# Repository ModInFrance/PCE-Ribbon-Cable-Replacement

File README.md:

# PCE-Ribbon-Cable-Replacement V2
A clean and simple solution to replace the massive ribbon cable in the PCE and Core Grafx.

This project is open source (please read the license). You can make your own or <a href="https://shop.modinfrance.fr/en/home/56-pc-engine-ribbon-cable-replacement.html" target="_blank">buy it from my store</a>.

The Original PCE (white) and the 2 CoreGrafx (blue and orange) remain beautiful pieces pf hardware after all those years.
However they have one major imperfection: The card connector and the main PCB are connected by a huge ribbon cable. This Ribbon cable tends to oxidize and break like a sheet of paper when opening the console.

This is why I created a replacement using two small PCBs and a single 45 pins FFC cable. The result is not only esthetically pleasing but also future proof.

<b>[UPDATE 12/01/2023]</b>
<b><u>V2 is out with a much smaller, leaner design</u></b>

<b><u>New pins - 2.5 mm</u></b>
I had some new pin array produced especially for the project. 2.5 pitch, 21 pins, extremely short upper pin. It removes most of the issues below, including the need for an isolation foam and trimming the pins. This is dead cheap, so contact me if you need some!

<b>CHALLENGES AND LIMITS OF THE SOLUTION</b>

- 2.5mm pitch<br />
Even though this is a relatively simple design the main challenge rest on the fact that the original Ribbon cable uses non-standard 2.5mm pitch when most of the hardware you can find out there is 2.54mm.
There is no magic solution but it's relatively easy to overcome the issue using standard 2.54 pin array and cutting them in half.

- PCBs contact<br />
Second issue is that the new cartridge connector PCB is sitting right on top the PCE extention connector when shell is closed. There can be contacts. This can easily be fixed with a 0.6mm PCB, a good trim of the pin arrays and, to be absolutely safe, adding a layer of foam on the extension port.

<b>INSTALLATION GUIDE</b>

Step 1 is to remove the original ribbon cable and believe me this is the hardest part of the mod. Take your time and don't pull too hard, you don't want too pull a pad or a trace.

Now get the kit. It should look like this (with an added piece of sticky foam). 

I suggest testing continuity now to make sure there was no error when soldering the Molex connector:
- Each PCB have 2 lines P101 and P102 and each line has 21 pins. 
- With the ribbon cable in. Pin 101-1 on the mobo adapter PCB should have good contact with Pin 101-1 on the catridge adapter PCB and the same for the other 41 pins

Now cut 2 11 pins long array and 2 10 pins array like this:

Trim the side of your arrays so that they can fit the PCE cartridge PCB (DO NOT SOLDER IT AT THIS STAGE)

You should have 2 very close pins due to the cut and the difference of pitch. 

Use your favorite clamp to bend them slightly so that you can nicely fit in the adapter PCB.

Solder all 42 pins on the top side of the adapter PCB

Trim the top of the soldered pins as short as possible

Repeat the process with the second adapter PCB and the Mobo of the PCE (and again remember to trim the soldered pins)

- And Finally solder the bottom side of the PCB
- Add the provided piece of foam to avoid contact with the extension port
- Connect the flat cable
- It should now look like this:

Last step : Play Jackie Chan's Action Kung Fu for the next 20 years.

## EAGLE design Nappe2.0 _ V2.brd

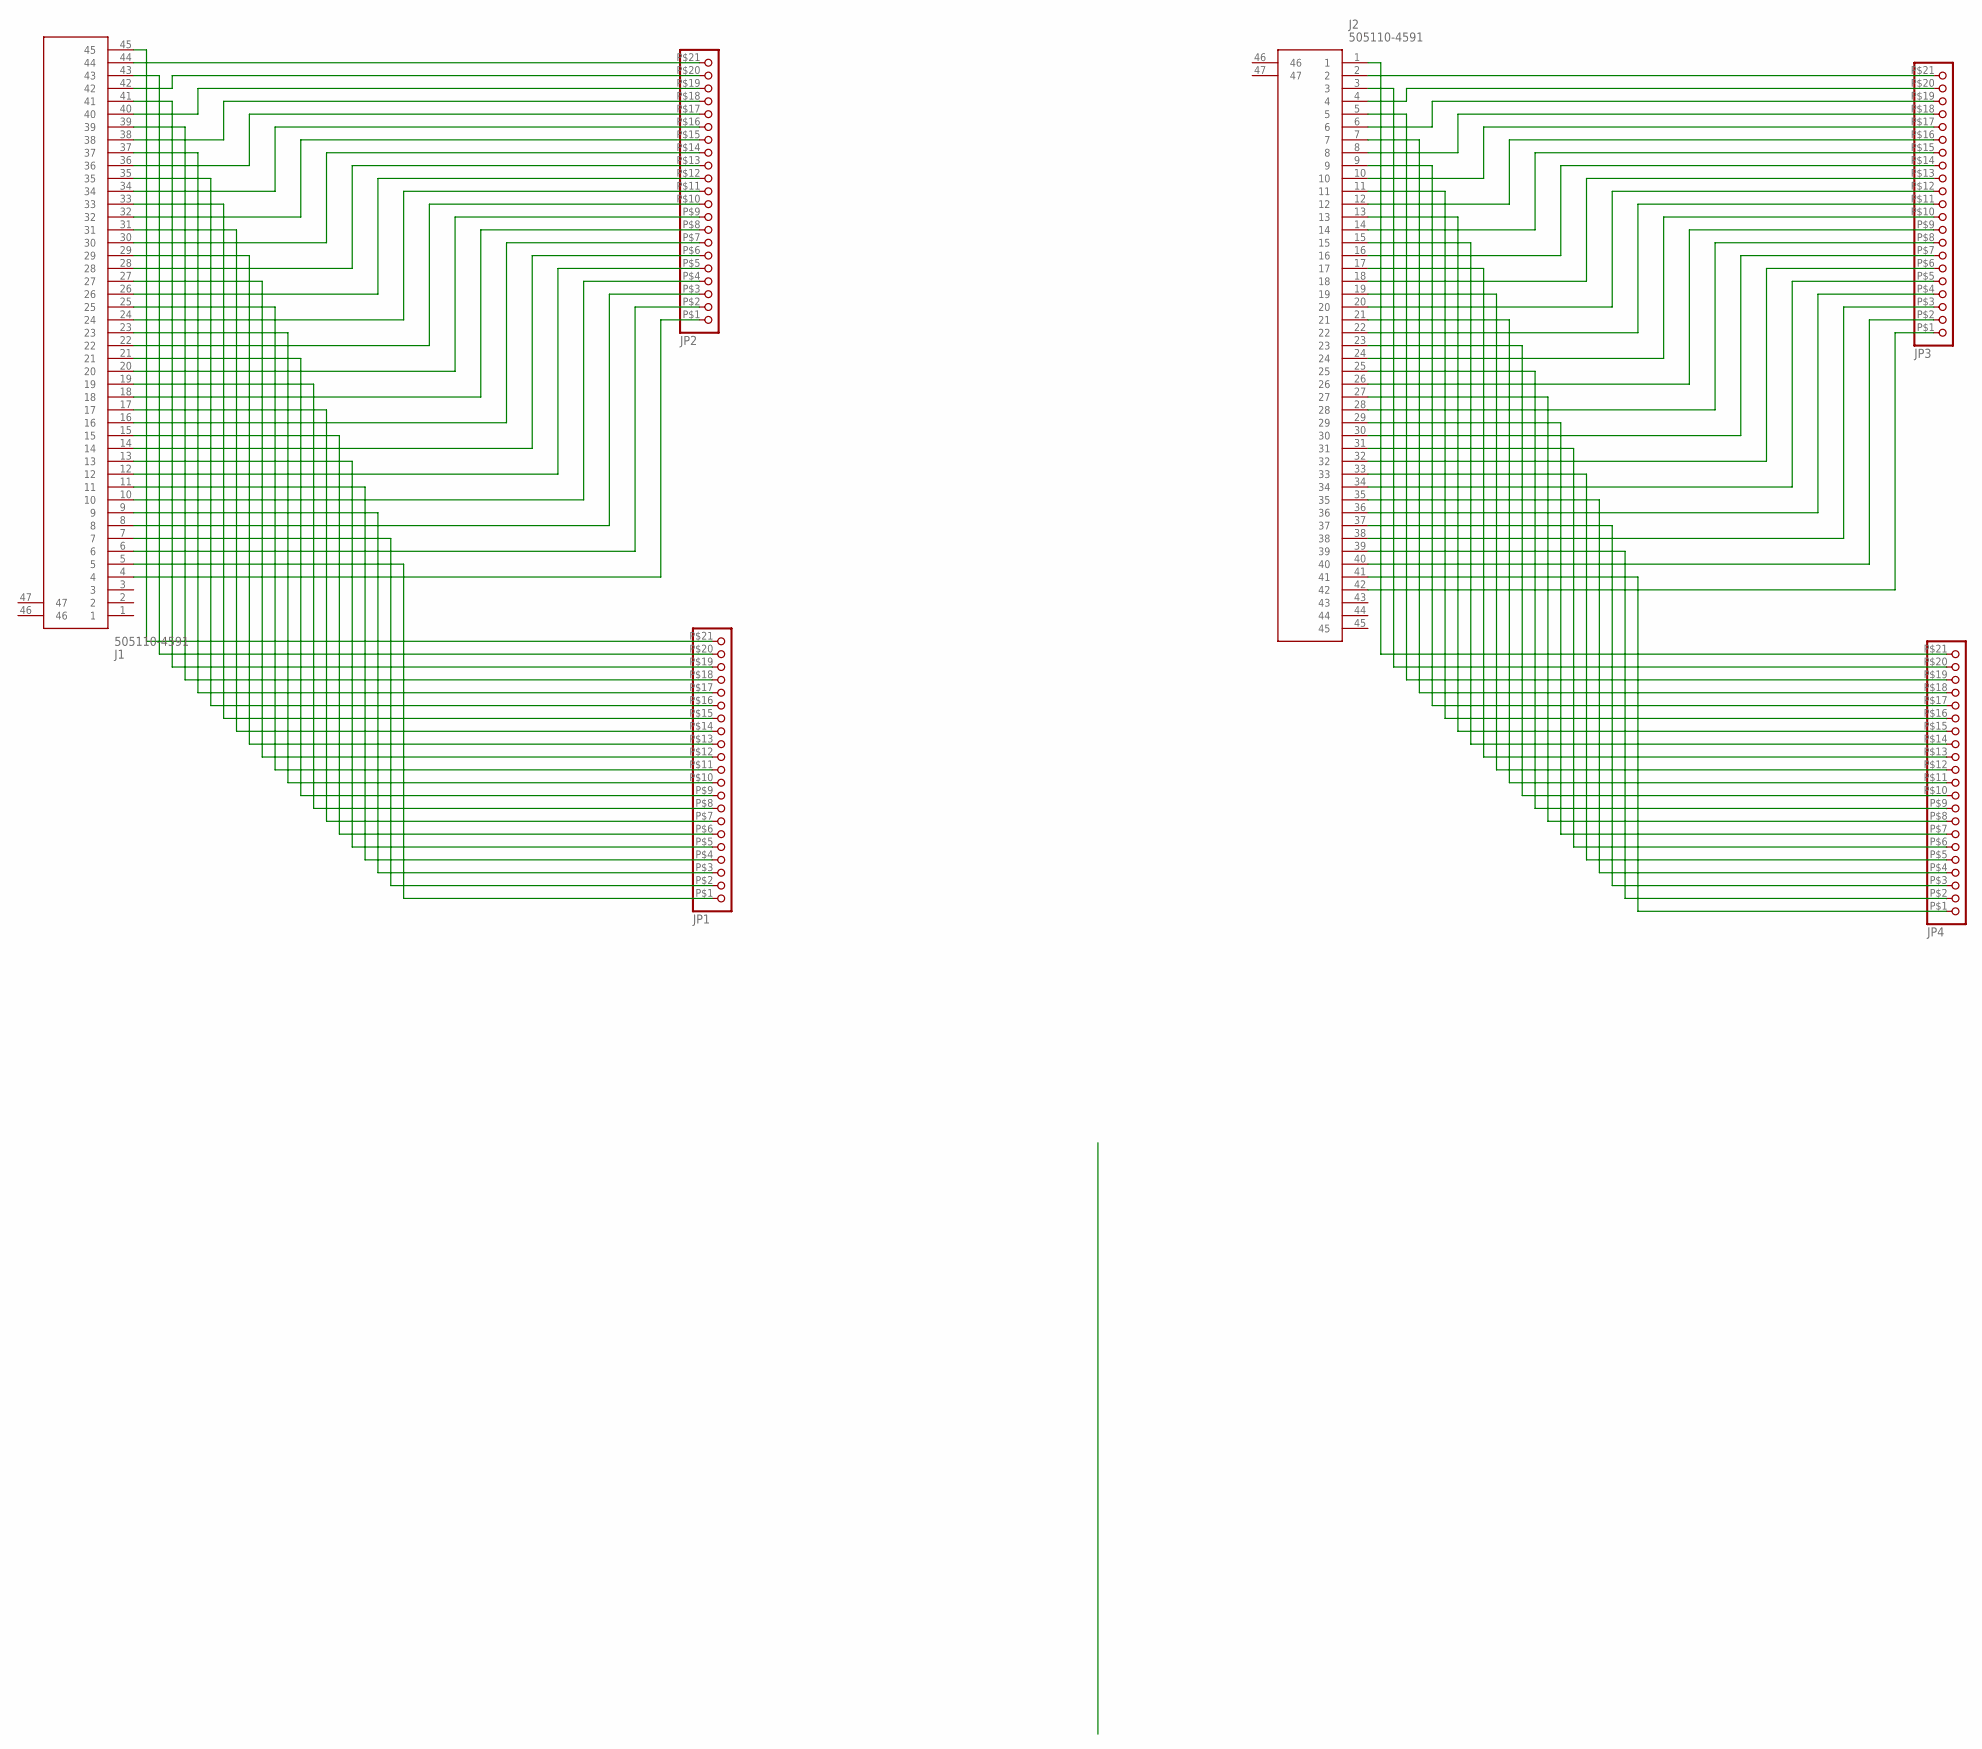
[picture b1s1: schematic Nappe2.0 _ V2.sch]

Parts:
J1, J2: 505110-4591; 5051104591
JP1, JP2, JP3, JP4: PINHD-1X21(2.5); 1X21(2.5)

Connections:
unnamed: J2.2, JP3.P$21 (21)
unnamed: J2.3, JP4.P$20 (20)
unnamed: J2.26, JP3.P$9 (9)
unnamed: J2.4, JP3.P$20 (20)
unnamed: J2.6, JP3.P$19 (19)
unnamed: J2.28, JP3.P$8 (8)
unnamed: J2.18, JP3.P$13 (13)
unnamed: J2.8, JP3.P$18 (18)
unnamed: J2.10, JP3.P$17 (17)
unnamed: J2.12, JP3.P$16 (16)
unnamed: J2.14, JP3.P$15 (15)
unnamed: J2.16, JP3.P$14 (14)
unnamed: J2.20, JP3.P$12 (12)
unnamed: J2.22, JP3.P$11 (11)
unnamed: J2.24, JP3.P$10 (10)
unnamed: J2.30, JP3.P$7 (7)
unnamed: J2.32, JP3.P$6 (6)
unnamed: J2.34, JP3.P$5 (5)
unnamed: J2.36, JP3.P$4 (4)
unnamed: J2.42, JP3.P$1 (1)
unnamed: J2.40, JP3.P$2 (2)
unnamed: J2.38, JP3.P$3 (3)
unnamed: J2.1, JP4.P$21 (21)
unnamed: J2.5, JP4.P$19 (19)
unnamed: J2.7, JP4.P$18 (18)
unnamed: J2.9, JP4.P$17 (17)
unnamed: J2.11, JP4.P$16 (16)
unnamed: J2.13, JP4.P$15 (15)
unnamed: J2.15, JP4.P$14 (14)
unnamed: J2.17, JP4.P$13 (13)
unnamed: J2.41, JP4.P$1 (1)
unnamed: J1.44, JP2.P$21 (21)
unnamed: J1.42, JP2.P$20 (20)
unnamed: J1.40, JP2.P$19 (19)
unnamed: J2.27, JP4.P$8 (8)
unnamed: J1.38, JP2.P$18 (18)
unnamed: J1.36, JP2.P$17 (17)
unnamed: J2.33, JP4.P$5 (5)
unnamed: J1.34, JP2.P$16 (16)
unnamed: J1.32, JP2.P$15 (15)
unnamed: J2.21, JP4.P$11 (11)
unnamed: J2.23, JP4.P$10 (10)
unnamed: J2.25, JP4.P$9 (9)
unnamed: J1.30, JP2.P$14 (14)
unnamed: J2.29, JP4.P$7 (7)
unnamed: J2.31, JP4.P$6 (6)
unnamed: J2.39, JP4.P$2 (2)
unnamed: J2.37, JP4.P$3 (3)
unnamed: J2.35, JP4.P$4 (4)
unnamed: J2.19, JP4.P$12 (12)
unnamed: J1.28, JP2.P$13 (13)
unnamed: J1.26, JP2.P$12 (12)
unnamed: J1.24, JP2.P$11 (11)
unnamed: J1.22, JP2.P$10 (10)
unnamed: J1.20, JP2.P$9 (9)
unnamed: J1.18, JP2.P$8 (8)
unnamed: J1.16, JP2.P$7 (7)
unnamed: J1.14, JP2.P$6 (6)
unnamed: J1.12, JP2.P$5 (5)
unnamed: J1.10, JP2.P$4 (4)
unnamed: J1.6, JP2.P$2 (2)
unnamed: J1.8, JP2.P$3 (3)
unnamed: J1.4, JP2.P$1 (1)
unnamed: J1.45, JP1.P$21 (21)
unnamed: J1.43, JP1.P$20 (20)
unnamed: J1.41, JP1.P$19 (19)
unnamed: J1.39, JP1.P$18 (18)
unnamed: J1.37, JP1.P$17 (17)
unnamed: J1.35, JP1.P$16 (16)
unnamed: J1.33, JP1.P$15 (15)
unnamed: J1.31, JP1.P$14 (14)
unnamed: J1.29, JP1.P$13 (13)
unnamed: J1.19, JP1.P$8 (8)
unnamed: J1.25, JP1.P$11 (11)
unnamed: J1.23, JP1.P$10 (10)
unnamed: J1.21, JP1.P$9 (9)
unnamed: J1.17, JP1.P$7 (7)
unnamed: J1.15, JP1.P$6 (6)
unnamed: J1.13, JP1.P$5 (5)
unnamed: J1.7, JP1.P$2 (2)
unnamed: J1.9, JP1.P$3 (3)
unnamed: J1.11, JP1.P$4 (4)
unnamed: J1.27, JP1.P$12 (12)
unnamed: J1.5, JP1.P$1 (1)

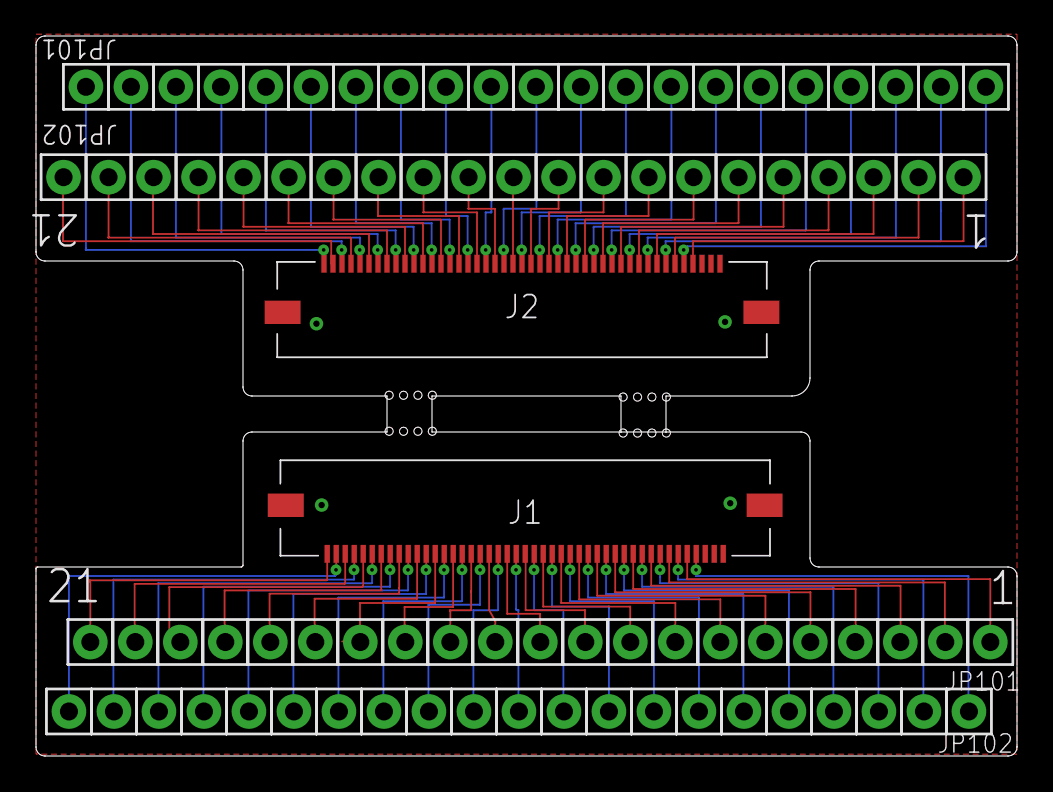
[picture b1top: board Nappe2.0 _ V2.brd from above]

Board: 2 copper layers, 54.5 x 40.0 mm, 6 parts (0 on the bottom side), 84 nets.

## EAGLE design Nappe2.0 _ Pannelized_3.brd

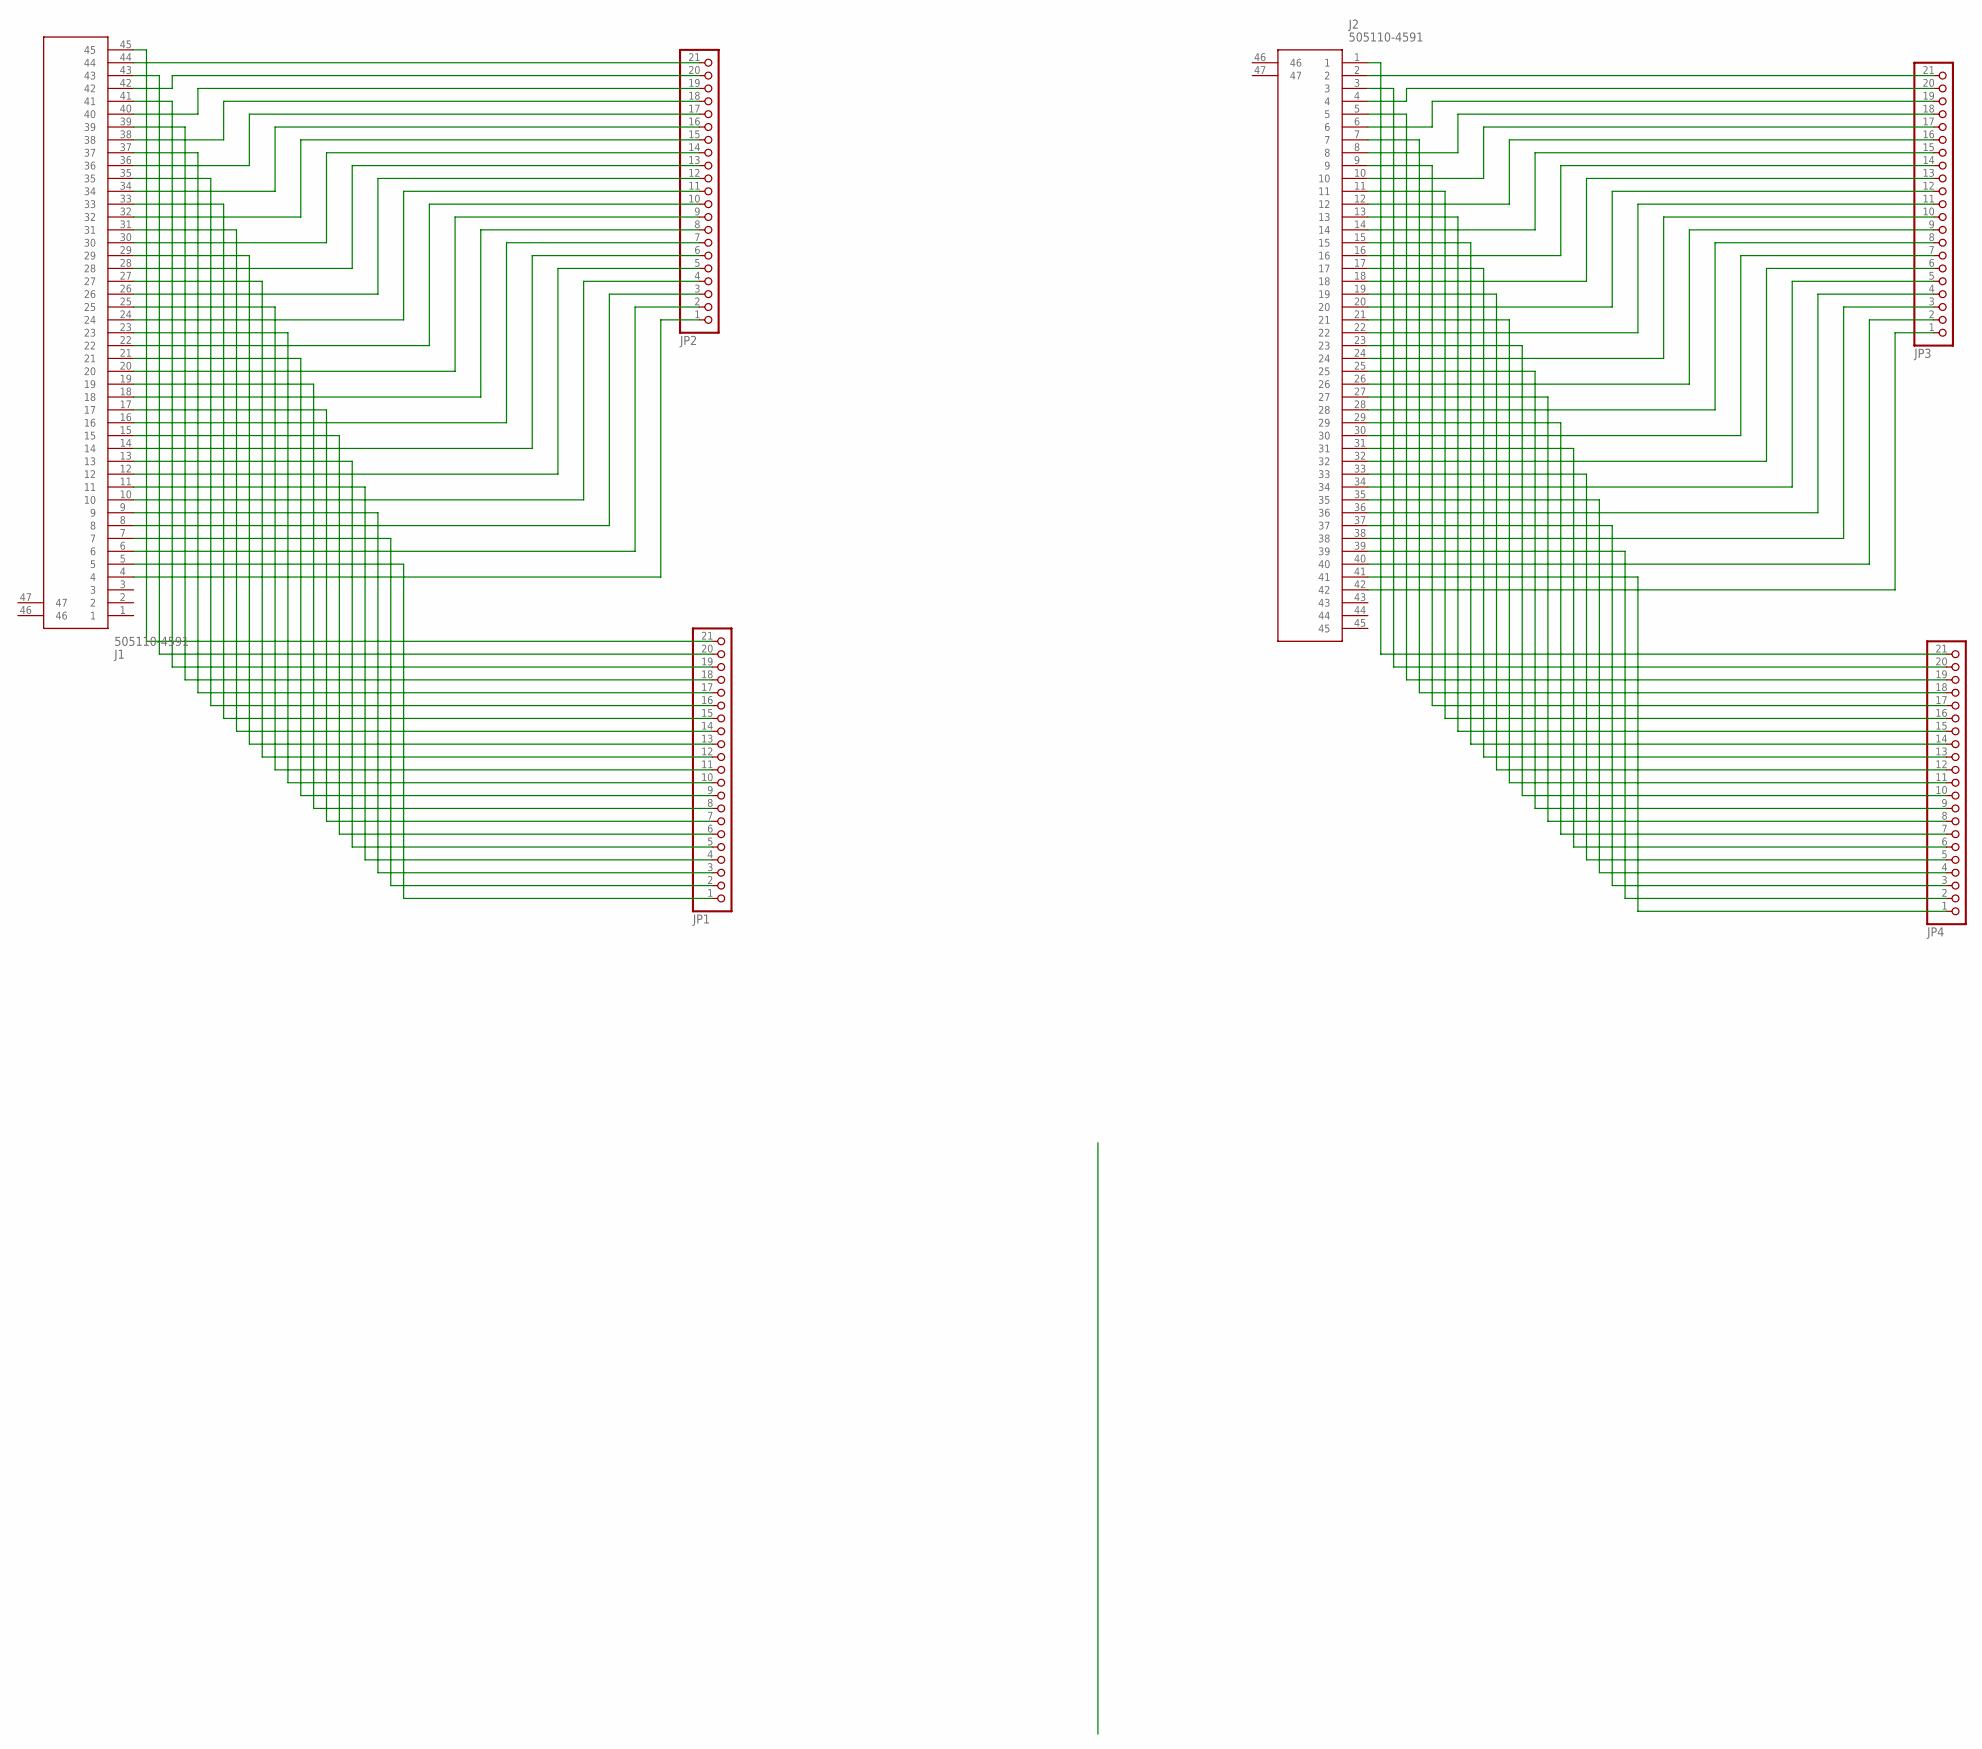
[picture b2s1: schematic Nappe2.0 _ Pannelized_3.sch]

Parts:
J1, J2: 505110-4591; 5051104591
JP1, JP2, JP3, JP4: PINHD-1X21(2.4); 1X21(2.4)

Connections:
unnamed: J2.2, JP3.21
unnamed: J2.3, JP4.20
unnamed: J2.26, JP3.9
unnamed: J2.4, JP3.20
unnamed: J2.6, JP3.19
unnamed: J2.28, JP3.8
unnamed: J2.18, JP3.13
unnamed: J2.8, JP3.18
unnamed: J2.10, JP3.17
unnamed: J2.12, JP3.16
unnamed: J2.14, JP3.15
unnamed: J2.16, JP3.14
unnamed: J2.20, JP3.12
unnamed: J2.22, JP3.11
unnamed: J2.24, JP3.10
unnamed: J2.30, JP3.7
unnamed: J2.32, JP3.6
unnamed: J2.34, JP3.5
unnamed: J2.36, JP3.4
unnamed: J2.42, JP3.1
unnamed: J2.40, JP3.2
unnamed: J2.38, JP3.3
unnamed: J2.1, JP4.21
unnamed: J2.5, JP4.19
unnamed: J2.7, JP4.18
unnamed: J2.9, JP4.17
unnamed: J2.11, JP4.16
unnamed: J2.13, JP4.15
unnamed: J2.15, JP4.14
unnamed: J2.17, JP4.13
unnamed: J2.41, JP4.1
unnamed: J1.44, JP2.21
unnamed: J1.42, JP2.20
unnamed: J1.40, JP2.19
unnamed: J2.27, JP4.8
unnamed: J1.38, JP2.18
unnamed: J1.36, JP2.17
unnamed: J2.33, JP4.5
unnamed: J1.34, JP2.16
unnamed: J1.32, JP2.15
unnamed: J2.21, JP4.11
unnamed: J2.23, JP4.10
unnamed: J2.25, JP4.9
unnamed: J1.30, JP2.14
unnamed: J2.29, JP4.7
unnamed: J2.31, JP4.6
unnamed: J2.39, JP4.2
unnamed: J2.37, JP4.3
unnamed: J2.35, JP4.4
unnamed: J2.19, JP4.12
unnamed: J1.28, JP2.13
unnamed: J1.26, JP2.12
unnamed: J1.24, JP2.11
unnamed: J1.22, JP2.10
unnamed: J1.20, JP2.9
unnamed: J1.18, JP2.8
unnamed: J1.16, JP2.7
unnamed: J1.14, JP2.6
unnamed: J1.12, JP2.5
unnamed: J1.10, JP2.4
unnamed: J1.6, JP2.2
unnamed: J1.8, JP2.3
unnamed: J1.4, JP2.1
unnamed: J1.45, JP1.21
unnamed: J1.43, JP1.20
unnamed: J1.41, JP1.19
unnamed: J1.39, JP1.18
unnamed: J1.37, JP1.17
unnamed: J1.35, JP1.16
unnamed: J1.33, JP1.15
unnamed: J1.31, JP1.14
unnamed: J1.29, JP1.13
unnamed: J1.19, JP1.8
unnamed: J1.25, JP1.11
unnamed: J1.23, JP1.10
unnamed: J1.21, JP1.9
unnamed: J1.17, JP1.7
unnamed: J1.15, JP1.6
unnamed: J1.13, JP1.5
unnamed: J1.7, JP1.2
unnamed: J1.9, JP1.3
unnamed: J1.11, JP1.4
unnamed: J1.27, JP1.12
unnamed: J1.5, JP1.1

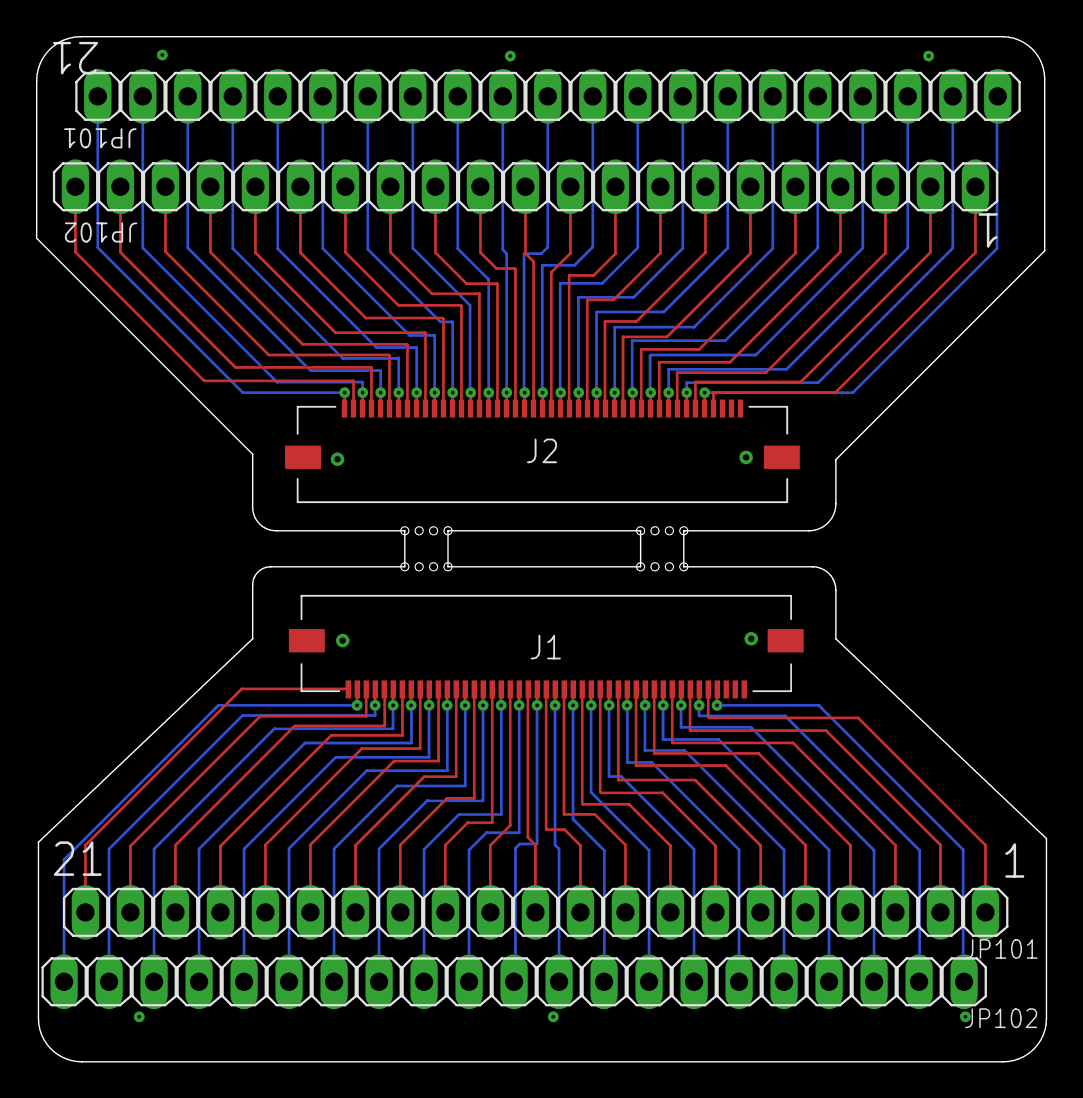
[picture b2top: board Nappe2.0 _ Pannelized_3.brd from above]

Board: 2 copper layers, 56.1 x 57.0 mm, 6 parts (0 on the bottom side), 84 nets.
